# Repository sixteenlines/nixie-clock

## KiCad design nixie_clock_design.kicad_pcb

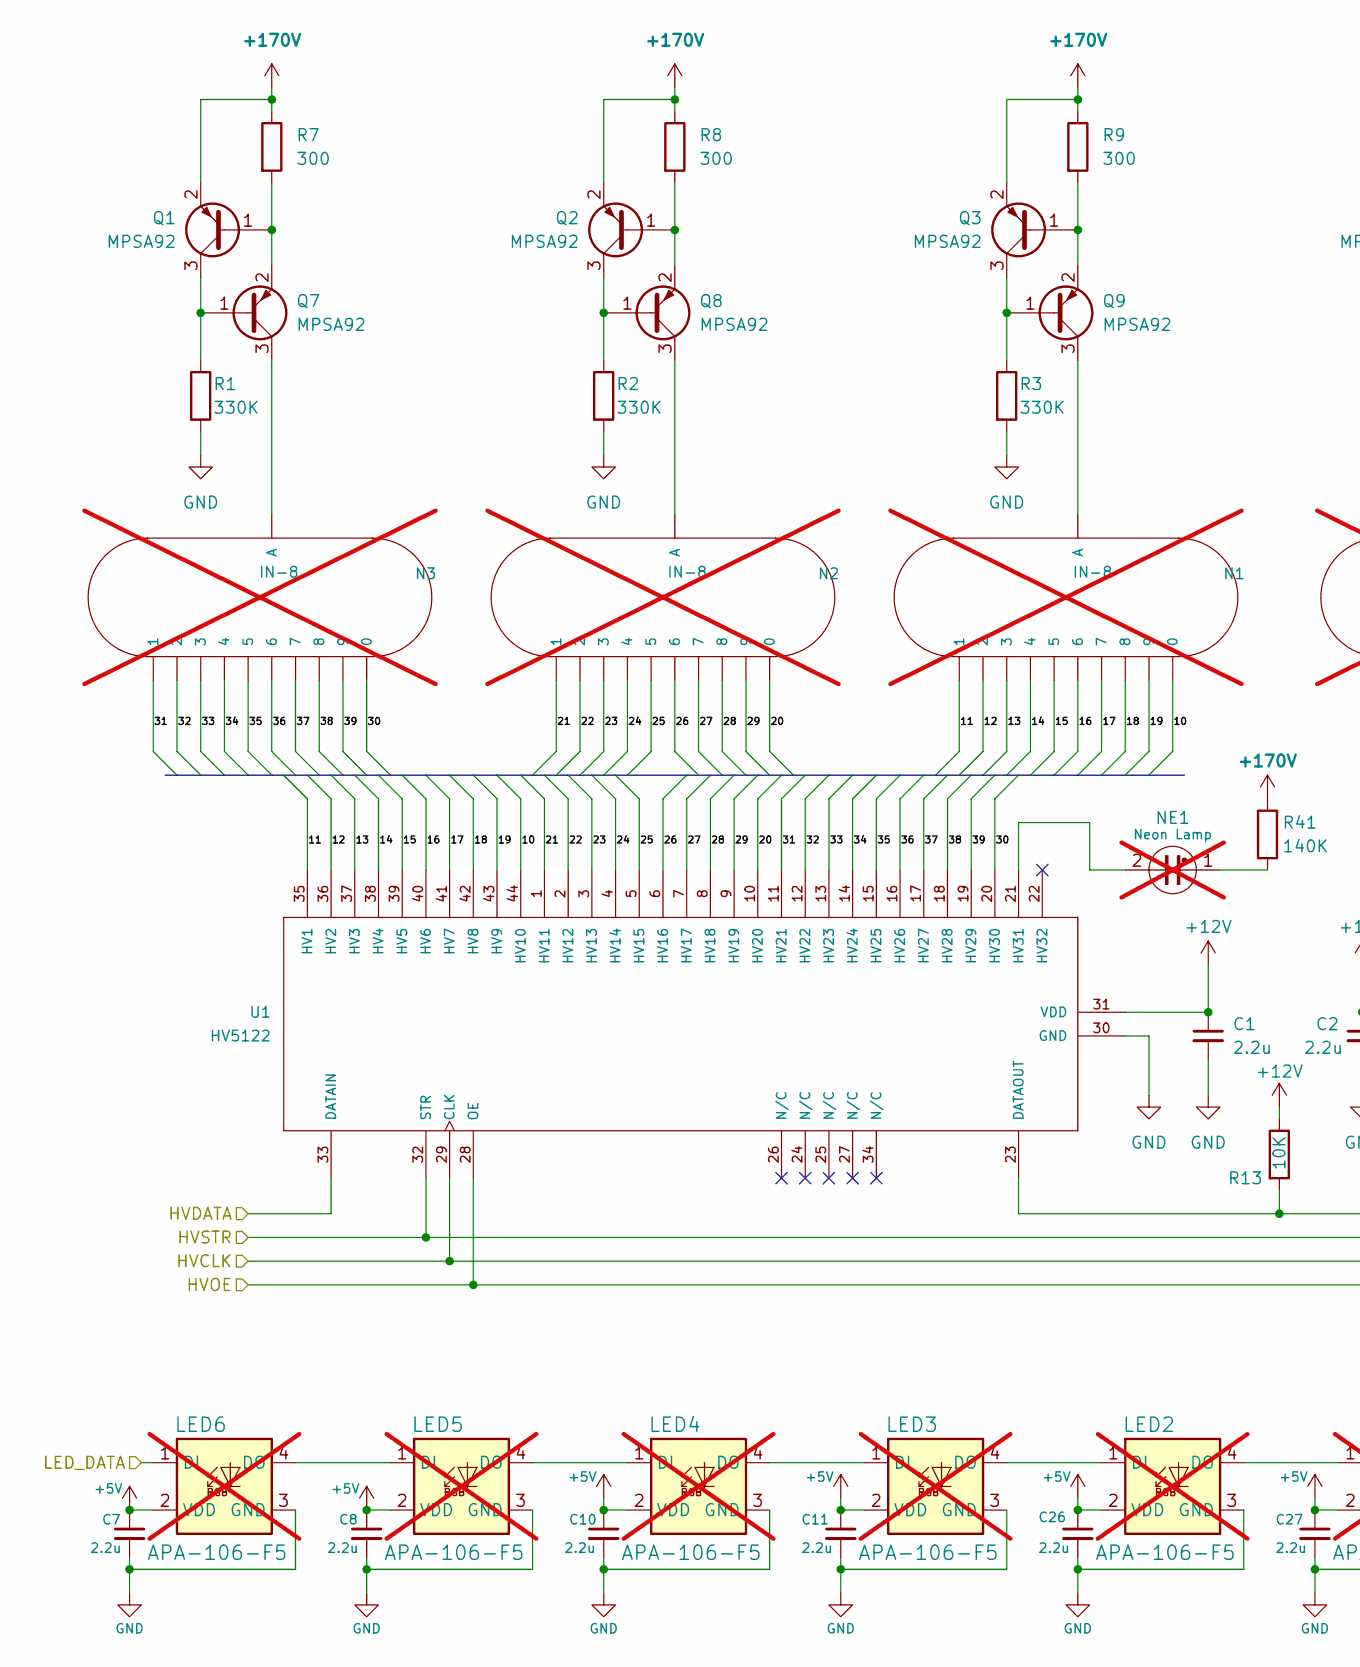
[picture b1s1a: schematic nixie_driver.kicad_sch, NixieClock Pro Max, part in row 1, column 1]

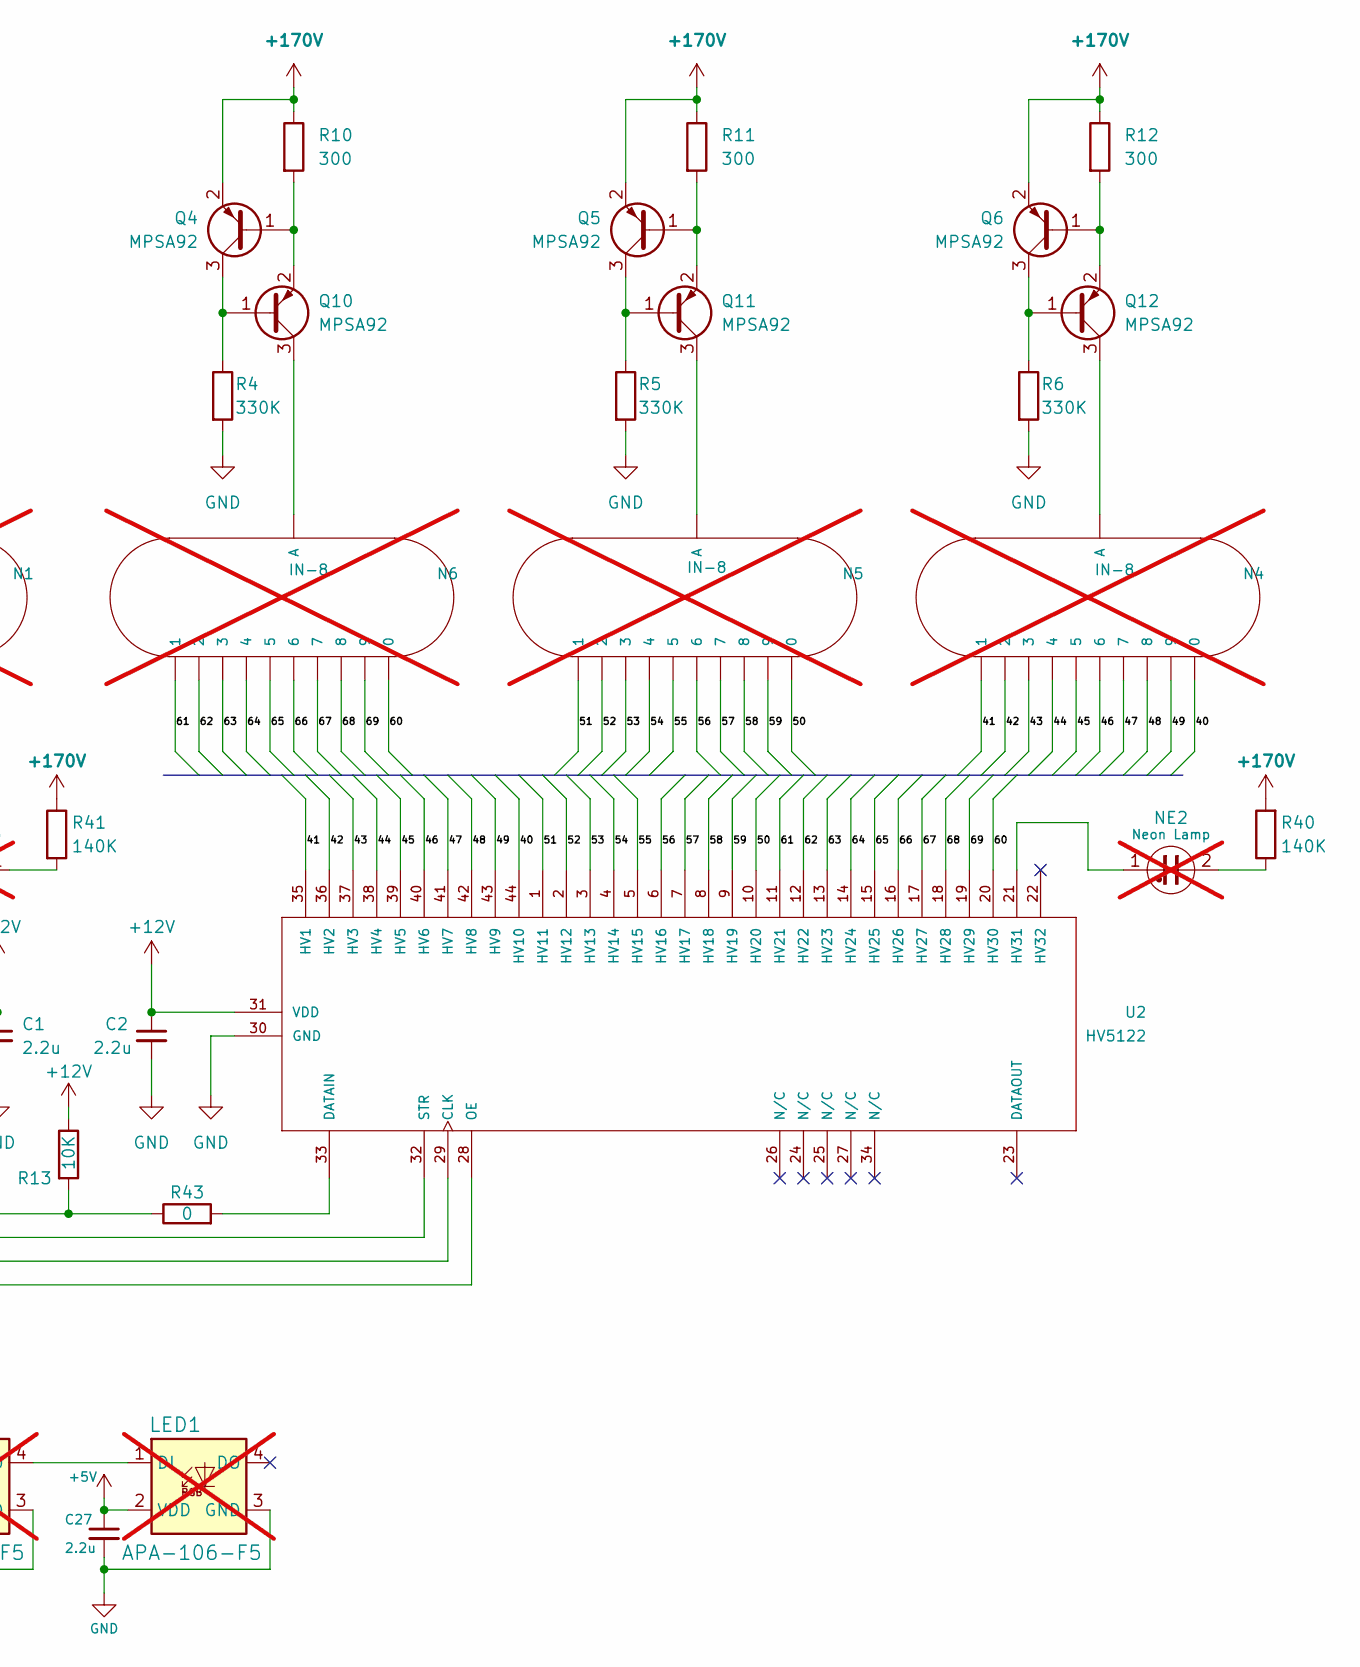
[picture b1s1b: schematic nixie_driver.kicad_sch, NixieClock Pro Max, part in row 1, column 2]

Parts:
C1, C2, C7, C8, C10, C11, C26, C27: 2.2u; C_0805_2012Metric; MPN C0805C225K8PACTU; LCSC Part Number C19110
LED1, LED2, LED3, LED4, LED5, LED6: APA-106-F5; LED_D5.0mm-4_RGB; MPN DNP; not fitted
N1, N2, N3, N4, N5, N6: IN-8; MPN DNP; not fitted
NE1, NE2: Neon Lamp; LED_D5.0mm; MPN DNP; not fitted
Q1, Q2, Q3, Q4, Q5, Q6, Q7, Q8, Q9, Q10, Q11, Q12: MPSA92; TO-92L_Inline_Wide; MPN MPSA92; LCSC Part Number C305412
R1, R2, R3, R4, R5, R6: 330K; R_1206_3216Metric; MPN RC1206JR-7W330KL; LCSC Part Number C137312
R7, R8, R9, R10, R11, R12: 300; R_1206_3216Metric; MPN CR1206-FX-3300ELF; LCSC Part Number C25374
R13: 10K; R_1206_3216Metric; MPN CRCW120610K0FKEA; LCSC Part Number C17902
R40, R41: 140K; R_0603_1608Metric; MPN RCS0603140KFKEA; LCSC Part Number C22875
R43: 0; R_0603_1608Metric; MPN MCT06030Z0000ZPW00; LCSC Part Number C21189
U1, U2: HV5122; PQFP-44_10x10mm_P0.8mm; MPN HV5122PJ-G; LCSC Part Number C646051

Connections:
+5V: C7.1, C8.1, C10.1, C11.1, C26.1, C27.1, LED1.2 (VDD), LED2.2 (VDD), LED3.2 (VDD), LED4.2 (VDD), LED5.2 (VDD), LED6.2 (VDD); also elsewhere on the board
+12V: C1.1, C2.1, R13.1, U1.31 (VDD), U2.31 (VDD); also elsewhere on the board
+170V: Q1.2 (E), Q2.2 (E), Q3.2 (E), Q4.2 (E), Q5.2 (E), Q6.2 (E), R7.1, R8.1, R9.1, R10.1, R11.1, R12.1, R40.2, R41.1; also elsewhere on the board
/Logic&PSU/HVCLK: U1.29 (CLK), U2.29 (CLK); also elsewhere on the board
/Logic&PSU/HVDATA: U1.33 (DATAIN); also elsewhere on the board
/Logic&PSU/HVOE: U1.28 (OE), U2.28 (OE); also elsewhere on the board
/Logic&PSU/HVSTR: U1.32 (STR), U2.32 (STR); also elsewhere on the board
/Logic&PSU/LED_DATA: LED6.1 (DI); also elsewhere on the board
/Nixie Driver/10: N1.0, U1.44 (HV10)
/Nixie Driver/11: N1.1, U1.35 (HV1)
/Nixie Driver/12: N1.2, U1.36 (HV2)
/Nixie Driver/13: N1.3, U1.37 (HV3)
/Nixie Driver/14: N1.4, U1.38 (HV4)
/Nixie Driver/15: N1.5, U1.39 (HV5)
/Nixie Driver/16: N1.6, U1.40 (HV6)
/Nixie Driver/17: N1.7, U1.41 (HV7)
/Nixie Driver/18: N1.8, U1.42 (HV8)
/Nixie Driver/19: N1.9, U1.43 (HV9)
/Nixie Driver/20: N2.0, U1.10 (HV20)
/Nixie Driver/21: N2.1, U1.1 (HV11)
/Nixie Driver/22: N2.2, U1.2 (HV12)
/Nixie Driver/23: N2.3, U1.3 (HV13)
/Nixie Driver/24: N2.4, U1.4 (HV14)
/Nixie Driver/25: N2.5, U1.5 (HV15)
/Nixie Driver/26: N2.6, U1.6 (HV16)
/Nixie Driver/27: N2.7, U1.7 (HV17)
/Nixie Driver/28: N2.8, U1.8 (HV18)
/Nixie Driver/29: N2.9, U1.9 (HV19)
/Nixie Driver/30: N3.0, U1.20 (HV30)
/Nixie Driver/31: N3.1, U1.11 (HV21)
/Nixie Driver/32: N3.2, U1.12 (HV22)
/Nixie Driver/33: N3.3, U1.13 (HV23)
/Nixie Driver/34: N3.4, U1.14 (HV24)
/Nixie Driver/35: N3.5, U1.15 (HV25)
/Nixie Driver/36: N3.6, U1.16 (HV26)
/Nixie Driver/37: N3.7, U1.17 (HV27)
/Nixie Driver/38: N3.8, U1.18 (HV28)
/Nixie Driver/39: N3.9, U1.19 (HV29)
/Nixie Driver/40: N4.0, U2.44 (HV10)
/Nixie Driver/41: N4.1, U2.35 (HV1)
/Nixie Driver/42: N4.2, U2.36 (HV2)
/Nixie Driver/43: N4.3, U2.37 (HV3)
/Nixie Driver/44: N4.4, U2.38 (HV4)
/Nixie Driver/45: N4.5, U2.39 (HV5)
/Nixie Driver/46: N4.6, U2.40 (HV6)
/Nixie Driver/47: N4.7, U2.41 (HV7)
/Nixie Driver/48: N4.8, U2.42 (HV8)
/Nixie Driver/49: N4.9, U2.43 (HV9)
/Nixie Driver/50: N5.0, U2.10 (HV20)
/Nixie Driver/51: N5.1, U2.1 (HV11)
/Nixie Driver/52: N5.2, U2.2 (HV12)
/Nixie Driver/53: N5.3, U2.3 (HV13)
/Nixie Driver/54: N5.4, U2.4 (HV14)
/Nixie Driver/55: N5.5, U2.5 (HV15)
/Nixie Driver/56: N5.6, U2.6 (HV16)
/Nixie Driver/57: N5.7, U2.7 (HV17)
/Nixie Driver/58: N5.8, U2.8 (HV18)
/Nixie Driver/59: N5.9, U2.9 (HV19)
/Nixie Driver/60: N6.0, U2.20 (HV30)
/Nixie Driver/61: N6.1, U2.11 (HV21)
/Nixie Driver/62: N6.2, U2.12 (HV22)
/Nixie Driver/63: N6.3, U2.13 (HV23)
/Nixie Driver/64: N6.4, U2.14 (HV24)
/Nixie Driver/65: N6.5, U2.15 (HV25)
/Nixie Driver/66: N6.6, U2.16 (HV26)
/Nixie Driver/67: N6.7, U2.17 (HV27)
/Nixie Driver/68: N6.8, U2.18 (HV28)
/Nixie Driver/69: N6.9, U2.19 (HV29)
GND: C1.2, C2.2, C7.2, C8.2, C10.2, C11.2, C26.2, C27.2, LED1.3 (GND), LED2.3 (GND), LED3.3 (GND), LED4.3 (GND), LED5.3 (GND), LED6.3 (GND), R1.2, R2.2, R3.2, R4.2, R5.2, R6.2, U1.30 (GND), U2.30 (GND); also elsewhere on the board
unnamed: LED1.1 (DI), LED2.4 (DO)
unnamed: LED2.1 (DI), LED3.4 (DO)
unnamed: LED3.1 (DI), LED4.4 (DO)
unnamed: LED4.1 (DI), LED5.4 (DO)
unnamed: LED5.1 (DI), LED6.4 (DO)
unnamed: NE1.1, R41.2
unnamed: NE2.2, R40.1
unnamed: Q1.1 (B), Q7.2 (E), R7.2
unnamed: Q1.3 (C), Q7.1 (B), R1.1
unnamed: Q2.1 (B), Q8.2 (E), R8.2
unnamed: Q2.3 (C), Q8.1 (B), R2.1
unnamed: Q3.1 (B), Q9.2 (E), R9.2
unnamed: Q3.3 (C), Q9.1 (B), R3.1
unnamed: N3.A, Q7.3 (C)
unnamed: N2.A, Q8.3 (C)
unnamed: N1.A, Q9.3 (C)
unnamed: Q4.3 (C), Q10.1 (B), R4.1
unnamed: N6.A, Q10.3 (C)
unnamed: Q4.1 (B), Q10.2 (E), R10.2
unnamed: Q5.3 (C), Q11.1 (B), R5.1
unnamed: N5.A, Q11.3 (C)
unnamed: Q5.1 (B), Q11.2 (E), R11.2
unnamed: Q6.3 (C), Q12.1 (B), R6.1
unnamed: N4.A, Q12.3 (C)
unnamed: Q6.1 (B), Q12.2 (E), R12.2
unnamed: R13.2, R43.1, U1.23 (DATAOUT)
unnamed: NE1.2, U1.21 (HV31)
unnamed: R43.2, U2.33 (DATAIN)
unnamed: NE2.1, U2.21 (HV31)

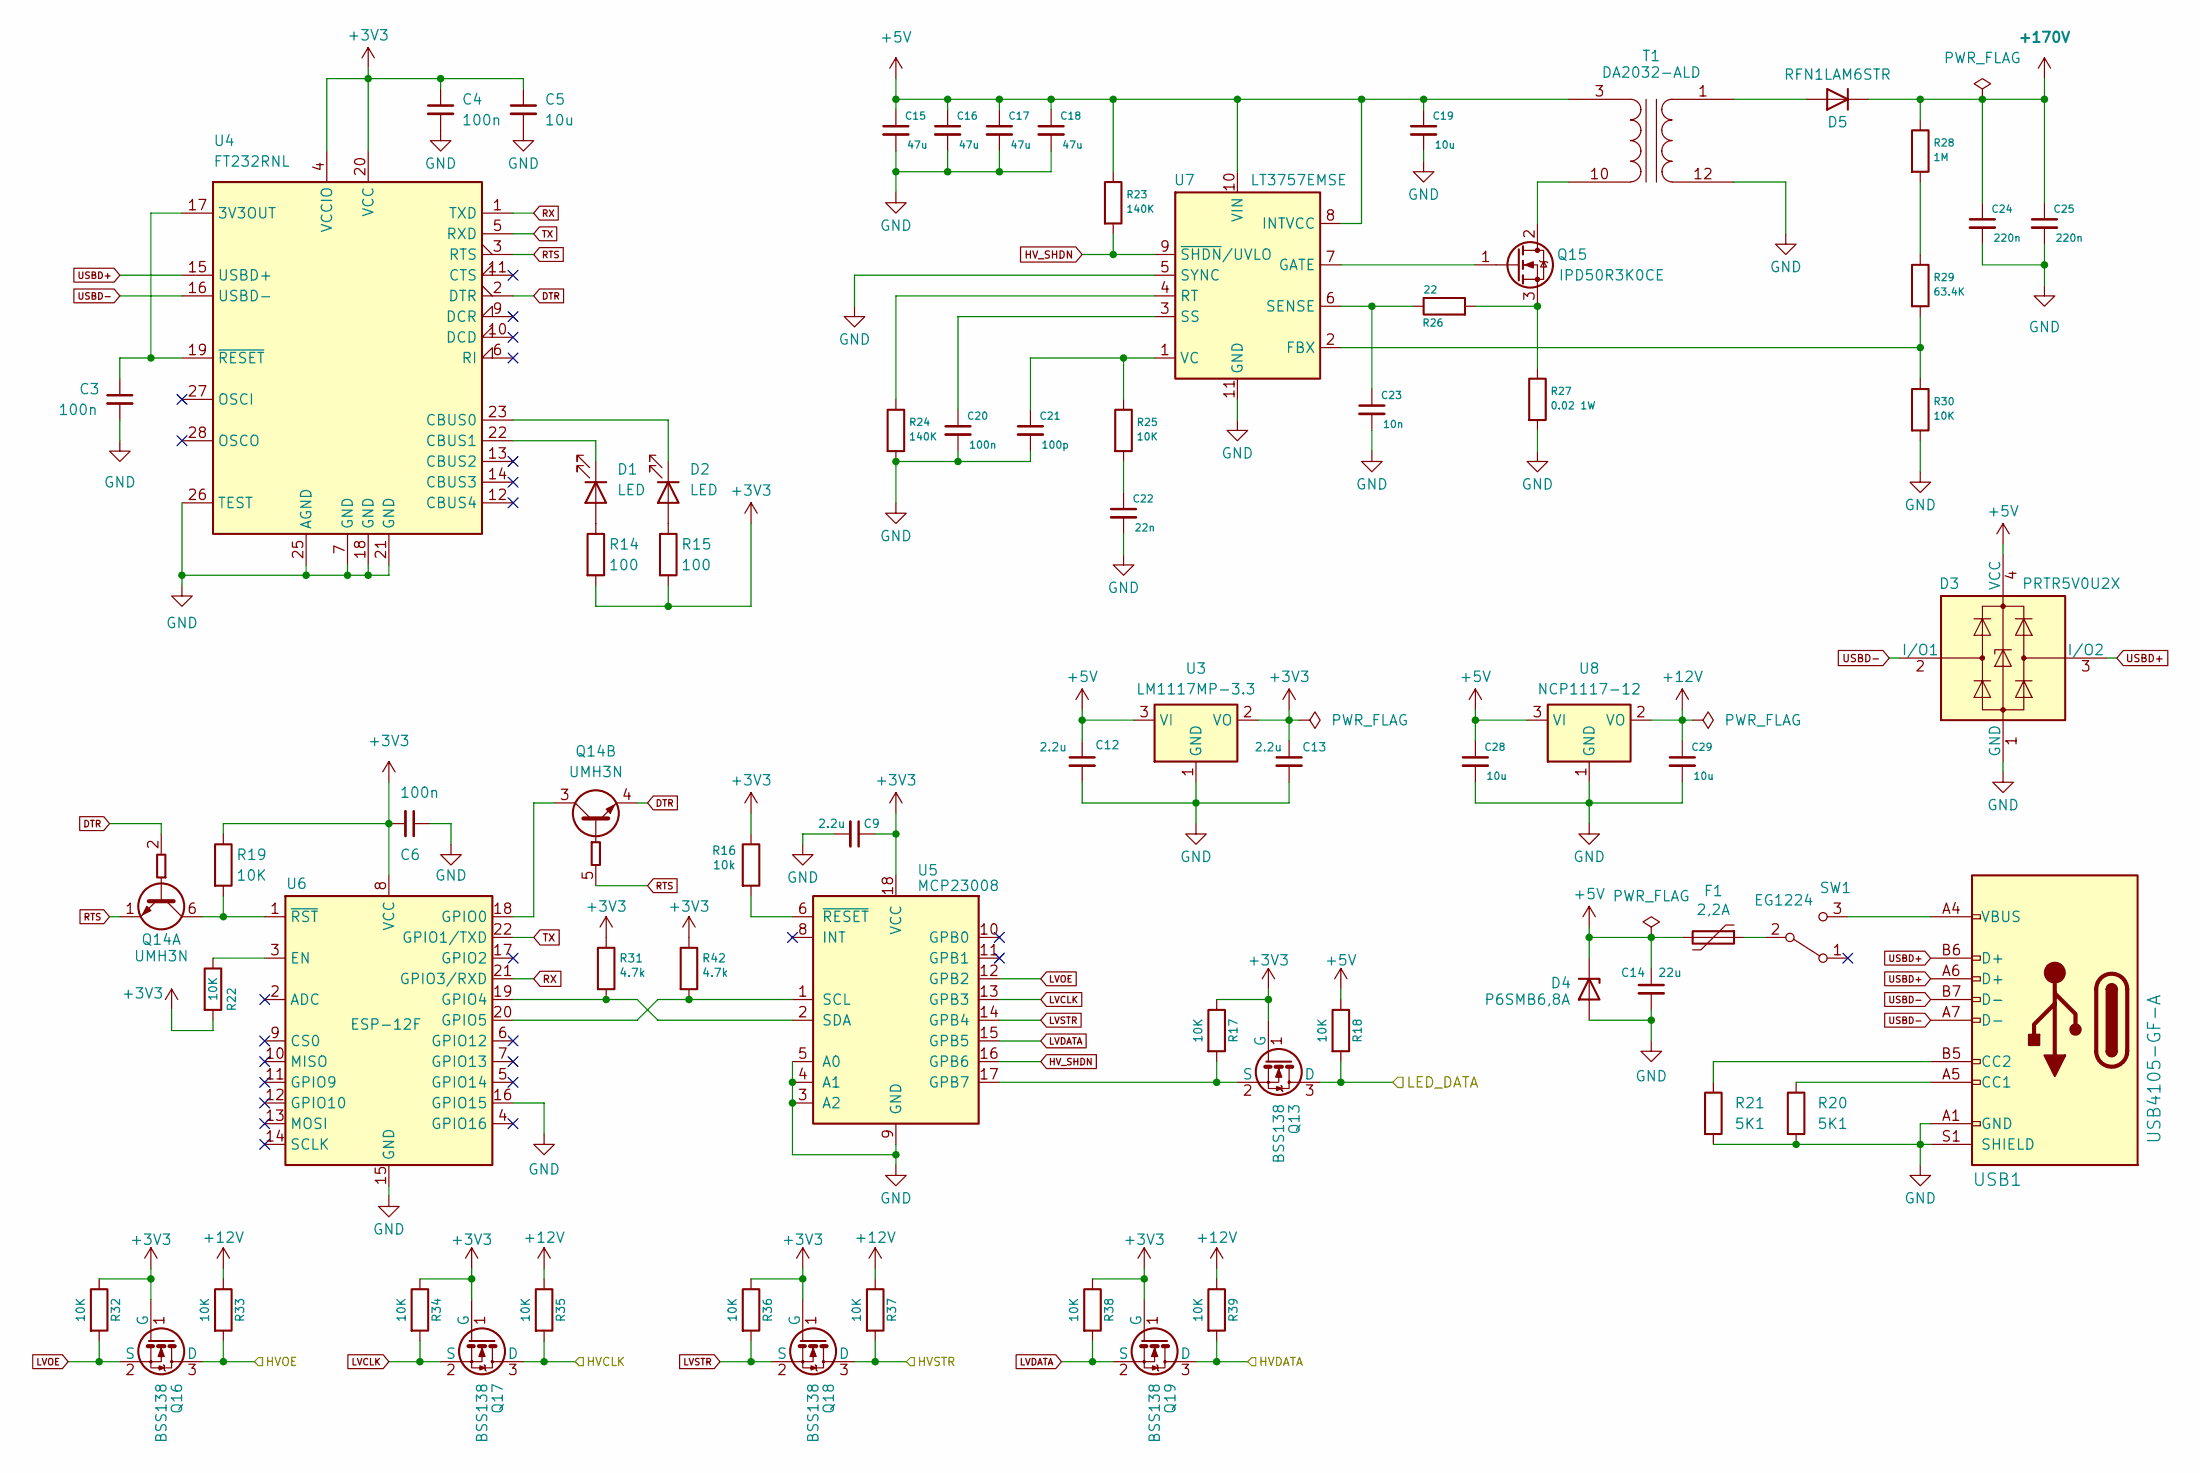
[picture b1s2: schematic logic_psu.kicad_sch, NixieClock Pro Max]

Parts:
C3, C4, C6: 100n; C_0603_1608Metric; MPN C0603C104K5RAC9109; LCSC Part Number C14663
C5: 10u; C_1206_3216Metric; MPN C1206C106K8RAC; LCSC Part Number C165101
C9, C12, C13: 2.2u; C_0805_2012Metric; MPN C0805C225K8PACTU; LCSC Part Number C19110
C14: 22u; C_0805_2012Metric; MPN GRM21BR60J226ME39L; LCSC Part Number C5674
C15, C16, C17, C18: 47u; C_1210_3225Metric; MPN GRM32ER71A476KE15L; LCSC Part Number C5189825
C19, C28, C29: 10u; C_0603_1608Metric; MPN GRM188C81A106MA73D; LCSC Part Number C85713
C20: 100n; CAPC1608X90N; MPN C0603C104K5RAC9109; LCSC Part Number C14663
C21: 100p; C_0603_1608Metric; MPN C0603C101K8RACAUTO; LCSC Part Number C1853160
C22: 22n; C_0603_1608Metric; MPN 0603ZC223KAT2A; LCSC Part Number C5128373
C23: 10n; C_0603_1608Metric; MPN 0603ZC103KAT4A; LCSC Part Number C519405
C24, C25: 220n; C_1206_3216Metric; MPN C1206C224KARACAUTO; LCSC Part Number C377089
D1: LED; LED_1206_3216Metric; MPN 599-0480-127F; LCSC Part Number C364563
D2: LED; LED_1206_3216Metric; MPN 599-0410-127F; LCSC Part Number C2981449
D3: PRTR5V0U2X; SOT-143; MPN PRTR5V0U2X-QR; LCSC Part Number C2827688
D4: P6SMB6,8A; D_SMB; MPN P6SMB6.8A/TR13; LCSC Part Number C707998
D5: RFN1LAM6STR; MPN RFN1LAM6STR; LCSC Part Number C962640
F1: 2,2A; Fuse_1812_4532Metric_Pad1.30x3.40mm_HandSolder; MPN MINISMDC110F/24-2; LCSC Part Number C2649922
Q13, Q16, Q17, Q18, Q19: BSS138; SOT-23W; MPN BSS138; LCSC Part Number C5224260
Q14: UMH3N; SOT-363_SC-70-6; MPN UMH3NTN; LCSC Part Number C123008
Q15: IPD50R3K0CE; TO-252-2; MPN IPD50R3K0CEAUMA1; LCSC Part Number C536788
R14, R15: 100; R_0603_1608Metric; MPN ESR03EZPF1000; LCSC Part Number C253328
R16: 10k; R_0603_1608Metric; MPN CMP0603AFX-1002ELF; LCSC Part Number C510087
R17, R18, R19, R22, R25, R30, R32, R33, R34, R35, R36, R37, R38, R39: 10K; R_0603_1608Metric; MPN CMP0603AFX-1002ELF; LCSC Part Number C510087
R20, R21: 5K1; R_0603_1608Metric; MPN ERJ-UP3J512V; LCSC Part Number C2091513
R23, R24: 140K; R_0603_1608Metric; MPN RCS0603140KFKEA; LCSC Part Number C22875
R26: 22; R_0603_1608Metric; MPN ERJ-PA3F22R0V; LCSC Part Number C873681
R27: 0.02 1W; R_1206_3216Metric; MPN CFN1206-JZ-R020ELF; LCSC Part Number C164156
R28: 1M; R_1206_3216Metric; MPN RCV12061M00FKEAAT; LCSC Part Number C17927
R29: 63.4K; R_0603_1608Metric; MPN CRCW060363K4FKEA; LCSC Part Number C23093
R31, R42: 4.7k; R_0603_1608Metric; MPN CRCW06034K70FKEAHP; LCSC Part Number C99782
SW1: EG1224; SW_E-Switch_EG1224_SPDT_Angled; MPN EG1224; LCSC Part Number C273395
T1: DA2032-ALD; SOP250P2197X889-12N; Mouser Part Number 994-DA2032-ALD
U3: LM1117MP-3.3; SOT-223-3_TabPin2; MPN LM1117MP-3.3/NOPB; LCSC Part Number C498153
U4: FT232RNL; SSOP-28_5.3x10.2mm_P0.65mm; MPN FT232RNL-REEL; LCSC Part Number C5246810
U5: MCP23008; SOIC-18W_7.5x11.6mm_P1.27mm; MPN MCP23008-E/SO; LCSC Part Number C92253
U6: ESP-12F; ESP-12E; MPN SBC-ESP8266-12F; LCSC Part Number C19949064
U7: LT3757EMSE; MSOP-10-1EP_3x3mm_P0.5mm_EP1.68x1.88mm; MPN LT3757EMSE; LCSC Part Number C580135
U8: NCP1117-12; SOT-223-3_TabPin2; MPN NCV1117ST12T3G; LCSC Part Number C179599
USB1: USB4105-GF-A; USB_C_Receptacle_GCT_USB4105-xx-A_16P_TopMnt_Horizontal; MPN USB4105-GF-A; LCSC Part Number C3020560

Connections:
+3V3: C4.1, C5.1, C6.2, C9.1, C13.1, Q13.1 (G), Q16.1 (G), Q17.1 (G), Q18.1 (G), Q19.1 (G), R14.2, R15.2, R16.1, R17.1, R19.1, R22.2, R31.1, R32.1, R34.1, R36.1, R38.1, R42.1, U3.2 (VO), U4.4 (VCCIO), U4.20 (VCC), U5.18 (VCC), U6.8 (VCC)
+5V: C12.1, C14.1, C15.1, C16.1, C17.1, C18.1, C19.1, C28.1, D3.4 (VCC), D4.1 (K), F1.2, R18.1, R23.1, T1.3 (AA), U3.3 (VI), U7.8 (INTVCC), U7.10 (VIN), U8.3 (VI); also elsewhere on the board
+12V: C29.1, R33.1, R35.1, R37.1, R39.1, U8.2 (VO); also elsewhere on the board
+170V: C24.1, C25.1, D5.1 (K), R28.1; also elsewhere on the board
/Logic&PSU/HVCLK: Q17.3 (D), R35.2; also elsewhere on the board
/Logic&PSU/HVDATA: Q19.3 (D), R39.2; also elsewhere on the board
/Logic&PSU/HVOE: Q16.3 (D), R33.2; also elsewhere on the board
/Logic&PSU/HVSTR: Q18.3 (D), R37.2; also elsewhere on the board
/Logic&PSU/LED_DATA: Q13.3 (D), R18.2; also elsewhere on the board
DTR: Q14.2 (B1), Q14.4 (E2), U4.2 (DTR)
GND: C3.2, C4.2, C5.2, C6.1, C9.2, C12.2, C13.2, C14.2, C15.2, C16.2, C17.2, C18.2, C19.2, C20.2, C21.2, C22.2, C23.2, C24.2, C25.2, C28.2, C29.2, D3.1 (GND), D4.2 (A), R20.2, R21.2, R24.2, R27.2, R30.2, T1.12 (SA), U3.1 (GND), U4.7 (GND), U4.18 (GND), U4.21 (GND), U4.25 (AGND), U4.26 (TEST), U5.3 (A2), U5.4 (A1), U5.5 (A0), U5.9 (GND), U6.15 (GND), U6.16 (GPIO15), U7.5 (SYNC), U7.11 (GND), U8.1 (GND), USB1.A1 (GND), USB1.A12 (GND), USB1.B1 (GND), USB1.B12 (GND), USB1.S1 (SHIELD); also elsewhere on the board
HV_SHDN: R23.2, U5.16 (GPB6), U7.9 (~SHDN/UVLO)
LVCLK: Q17.2 (S), R34.2, U5.13 (GPB3)
LVDATA: Q19.2 (S), R38.2, U5.15 (GPB5)
LVOE: Q16.2 (S), R32.2, U5.12 (GPB2)
LVSTR: Q18.2 (S), R36.2, U5.14 (GPB4)
unnamed: C22.1, R25.2
unnamed: D1.2 (A), R14.1
unnamed: D1.1 (K), U4.22 (CBUS1)
unnamed: D2.2 (A), R15.1
unnamed: D2.1 (K), U4.23 (CBUS0)
unnamed: D5.2 (A), T1.1 (SB)
unnamed: Q13.2 (S), R17.2, U5.17 (GPB7)
unnamed: Q14.6 (C1), R19.2, U6.1 (~RST)
unnamed: Q14.3 (C2), U6.18 (GPIO0)
unnamed: Q15.2 (D), T1.10 (AB)
unnamed: Q15.1 (G), U7.7 (GATE)
unnamed: Q15.3 (S), R26.2, R27.1
unnamed: R28.2, R29.1
unnamed: F1.1, SW1.2 (B)
unnamed: SW1.3 (C), USB1.A4 (VBUS), USB1.A9 (VBUS), USB1.B4 (VBUS), USB1.B9 (VBUS)
unnamed: C3.1, U4.17 (3V3OUT), U4.19 (~RESET)
unnamed: R42.2, U5.1 (SCL), U6.20 (GPIO5)
unnamed: R31.2, U5.2 (SDA), U6.19 (GPIO4)
unnamed: R16.2, U5.6 (~RESET)
unnamed: R22.1, U6.3 (EN)
unnamed: R29.2, R30.1, U7.2 (FBX)
unnamed: R24.1, U7.4 (RT)
unnamed: C23.1, R26.1, U7.6 (SENSE)
unnamed: C20.1, U7.3 (SS)
unnamed: C21.1, R25.1, U7.1 (VC)
unnamed: R20.1, USB1.A5 (CC1)
unnamed: R21.1, USB1.B5 (CC2)
RTS: Q14.1 (E1), Q14.5 (B2), U4.3 (RTS)
RX: U4.1 (TXD), U6.21 (GPIO3/RXD)
TX: U4.5 (RXD), U6.22 (GPIO1/TXD)
USBD+: D3.3 (I/O2), U4.15 (USBD+), USB1.A6 (D+), USB1.B6 (D+)
USBD-: D3.2 (I/O1), U4.16 (USBD-), USB1.A7 (D-), USB1.B7 (D-)

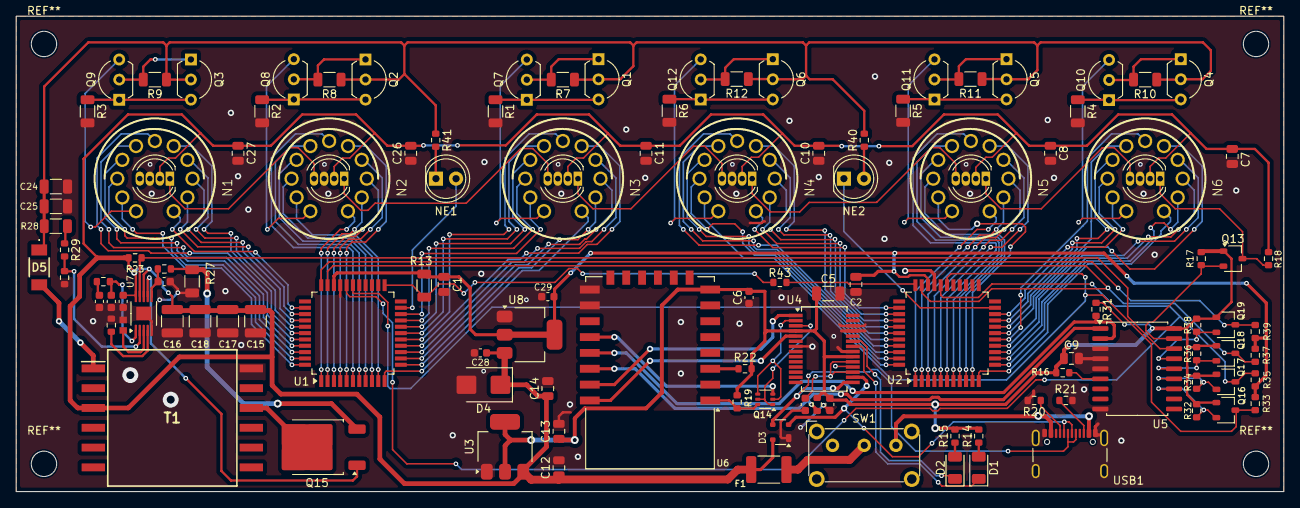
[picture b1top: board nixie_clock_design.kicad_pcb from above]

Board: 2 copper layers, 160.0 x 60.0 mm, 122 parts (0 on the bottom side), 137 nets.

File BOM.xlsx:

Reference | Value | Footprint | Qty | DNP | MPN | LCSC
C1,C2,C7,C8,C9,C10,C11,C12,C13,C26,C27 | 2.2u | Capacitor_SMD:C_0805_2012Metric | 11 |  | C0805C225K8PACTU | C19110
C3,C4,C6 | 100n | Capacitor_SMD:C_0603_1608Metric | 3 |  | C0603C104K5RAC9109 | C14663
C5 | 10u | Capacitor_SMD:C_1206_3216Metric | 1 |  | C1206C106K8RAC | C165101
C14 | 22u | Capacitor_SMD:C_0805_2012Metric | 1 |  | GRM21BR60J226ME39L | C5674
C15,C16,C17,C18 | 47u | Capacitor_SMD:C_1210_3225Metric | 4 |  | GRM32ER71A476KE15L | C5189825
C19,C28,C29 | 10u | Capacitor_SMD:C_0603_1608Metric | 3 |  | GRM188C81A106MA73D | C85713
C20 | 100n | Mouser:CAPC1608X90N | 1 |  | C0603C104K5RAC9109 | C14663
C21 | 100p | Capacitor_SMD:C_0603_1608Metric | 1 |  | C0603C101K8RACAUTO | C1853160
C22 | 22n | Capacitor_SMD:C_0603_1608Metric | 1 |  | 0603ZC223KAT2A | C5128373
C23 | 10n | Capacitor_SMD:C_0603_1608Metric | 1 |  | 0603ZC103KAT4A | C519405
C24,C25 | 220n | Capacitor_SMD:C_1206_3216Metric | 2 |  | C1206C224KARACAUTO | C377089
D1 | LED | LED_SMD:LED_1206_3216Metric | 1 |  | 599-0480-127F | C364563
D2 | LED | LED_SMD:LED_1206_3216Metric | 1 |  | 599-0410-127F | C2981449
D3 | PRTR5V0U2X | Package_TO_SOT_SMD:SOT-143 | 1 |  | PRTR5V0U2X-QR | C2827688
D4 | P6SMB6,8A | Diode_SMD:D_SMB | 1 |  | P6SMB6.8A/TR13 | C707998
D5 | RFN1LAM6STR | footprints:RFN1LAM6STR | 1 |  | RFN1LAM6STR | C962640
F1 | 2,2A | Fuse:Fuse_1812_4532Metric_Pad1.30x3.40mm_HandSolder | 1 |  | MINISMDC110F/24-2 | C2649922
LED1,LED2,LED3,LED4,LED5,LED6 | APA-106-F5 | LED_THT:LED_D5.0mm-4_RGB | 6 | Nicht bestücken | DNP
N1,N2,N3,N4,N5,N6 | IN-8 | nixies-us:IN-8 | 6 | Nicht bestücken | DNP
NE1,NE2 | Neon Lamp | LED_THT:LED_D5.0mm | 2 | Nicht bestücken | DNP
Q1,Q2,Q3,Q4,Q5,Q6,Q7,Q8,Q9,Q10,Q11,Q12 | MPSA92 | Package_TO_SOT_THT:TO-92L_Inline_Wide | 12 |  | MPSA92 | C305412
Q13,Q16,Q17,Q18,Q19 | BSS138 | Package_TO_SOT_SMD:SOT-23W | 5 |  | BSS138 | C5224260
Q14 | UMH3N | Package_TO_SOT_SMD:SOT-363_SC-70-6 | 1 |  | UMH3NTN | C123008
Q15 | IPD50R3K0CE | Package_TO_SOT_SMD:TO-252-2 | 1 |  | IPD50R3K0CEAUMA1
R1,R2,R3,R4,R5,R6 | 330K | Resistor_SMD:R_1206_3216Metric | 6 |  | RC1206JR-7W330KL
R7,R8,R9,R10,R11,R12 | 300 | Resistor_SMD:R_1206_3216Metric | 6 |  | CR1206-FX-3300ELF
R13 | 10K | Resistor_SMD:R_1206_3216Metric | 1 |  | CRCW120610K0FKEA
R14,R15 | 100 | Resistor_SMD:R_0603_1608Metric | 2 |  | ESR03EZPF1000
R16 | 10k | Resistor_SMD:R_0603_1608Metric | 1 |  | CMP0603AFX-1002ELF
R17,R18,R19,R22,R25,R30,R32,R33,R34,R35,R36,R37,R38,R39 | 10K | Resistor_SMD:R_0603_1608Metric | 14 |  | CMP0603AFX-1002ELF
R20,R21 | 5K1 | Resistor_SMD:R_0603_1608Metric | 2 |  | ERJ-UP3J512V
R23,R24,R40,R41 | 140K | Resistor_SMD:R_0603_1608Metric | 4 |  | RCS0603140KFKEA
R26 | 22 | Resistor_SMD:R_0603_1608Metric | 1 |  | ERJ-PA3F22R0V
R27 | 0.02 1W | Resistor_SMD:R_1206_3216Metric | 1 |  | CFN1206-JZ-R020ELF
R28 | 1M | Resistor_SMD:R_1206_3216Metric | 1 |  | RCV12061M00FKEAAT
R29 | 63.4K | Resistor_SMD:R_0603_1608Metric | 1 |  | CRCW060363K4FKEA
R31,R42 | 4.7k | Resistor_SMD:R_0603_1608Metric | 2 |  | CRCW06034K70FKEAHP
SW1 | EG1224 | Button_Switch_THT:SW_E-Switch_EG1224_SPDT_Angled | 1 |  | EG1224 | C273395
T1 | DA2032-ALD | footprints:SOP250P2197X889-12N | 1 |  | DA2032-ALD | C7938441
U1,U2 | HV5122 | Package_QFP:PQFP-44_10x10mm_P0.8mm | 2 |  | HV5122PJ-G | C646051
U3 | LM1117MP-3.3 | Package_TO_SOT_SMD:SOT-223-3_TabPin2 | 1 |  | LM1117MP-3.3/NOPB | C498153
U4 | FT232RNL | Package_SO:SSOP-28_5.3x10.2mm_P0.65mm | 1 |  | FT232RNL-REEL | C5246810
U5 | MCP23008 | Package_SO:SOIC-18W_7.5x11.6mm_P1.27mm | 1 |  | MCP23008-E/SO | C92253
U6 | ESP-12F | RF_Module:ESP-12E | 1 |  | SBC-ESP8266-12F | C19949064
U7 | LT3757EMSE | Package_SO:MSOP-10-1EP_3x3mm_P0.5mm_EP1.68x1.88mm | 1 |  | LT3757EMSE | C580135
U8 | NCP1117-12 | Package_TO_SOT_SMD:SOT-223-3_TabPin2 | 1 |  | NCV1117ST12T3G | C179599
USB1 | USB4105-GF-A | Connector_USB:USB_C_Receptacle_GCT_USB4105-xx-A_16P_TopMnt_Horizontal | 1 |  | USB4105-GF-A | C3020560

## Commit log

2024-03-20 prototype v0.5
2024-03-27 fixed pull-ups
2024-03-27 fixed 5V connection
2024-04-02 added HV5122 data line shunt
2024-08-23 updated lcsc parts
